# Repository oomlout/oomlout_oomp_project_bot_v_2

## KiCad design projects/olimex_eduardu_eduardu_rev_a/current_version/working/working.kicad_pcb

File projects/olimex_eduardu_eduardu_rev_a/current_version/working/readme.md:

# eduardu
 
## summary 
* id: olimex_eduardu_eduardu_rev_a
* user: olimex
* name: eduardu
* board: eduardu_rev_a
* repo: https://github.com/OLIMEX/eduArdu
* src_file_repo_kicad_pcb: HARDWARE/eduArdu_Rev_A/eduArdu_Rev_A.kicad_pcb
* src_file_repo_kicad_pcb_link: https://github.com/OLIMEX/eduArdu/tree/master/HARDWARE/eduArdu_Rev_A/eduArdu_Rev_A.kicad_pcb

* src_file_repo_sch: HARDWARE/eduArdu_Rev_A/eduArdu_Rev_A.sch
* src_file_repo_sch_link: https://github.com/OLIMEX/eduArdu/tree/master/HARDWARE/eduArdu_Rev_A/eduArdu_Rev_A.sch
* full details link: https://github.com/oomlout/oomlout_oomp_project_bot_v_2/tree/main/projects/olimex_eduardu_eduardu_rev_a/current_version/working

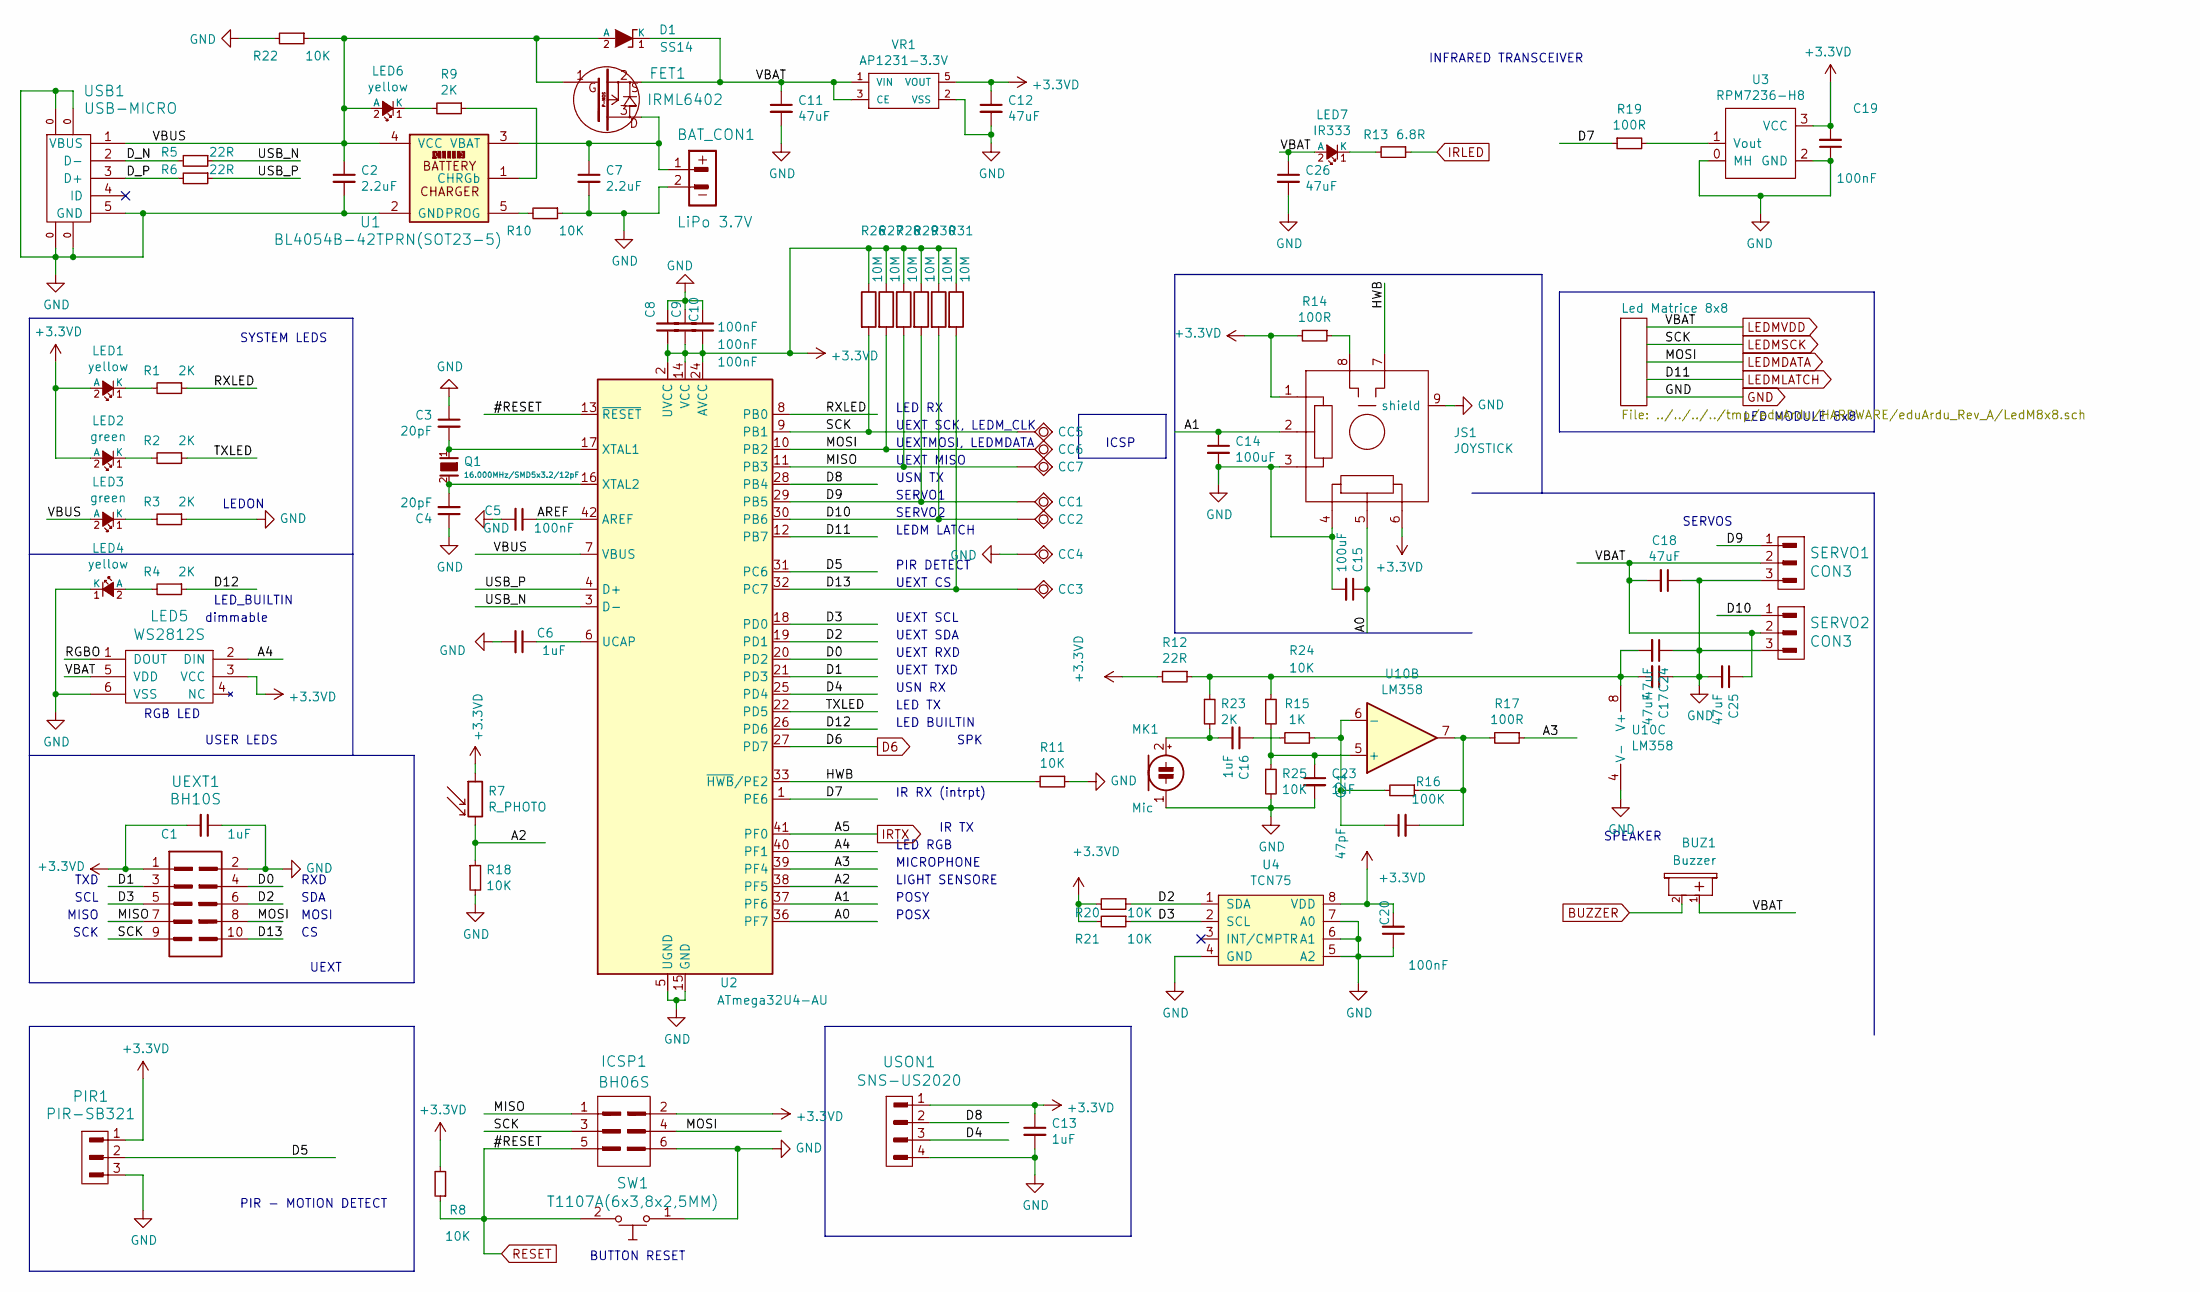
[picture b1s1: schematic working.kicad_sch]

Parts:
BAT_CON1: LiPo 3.7V; LIPO_BAT-CON2DW02R
BUZ1: Buzzer; BUZZER-PB1240
C1, C6, C13, C16, C23: 1uF; C_0603_5MIL_DWS
C2, C7: 2.2uF; C_0603_5MIL_DWS
C3, C4: 20pF; C_0402_5MIL_DWS
C5, C8, C9, C10, C19, C20: 100nF; C_0402_5MIL_DWS
C11, C12, C18, C26: 47uF; C_0805_5MIL_DWS
C14, C15: 100uF; C_0402_5MIL_DWS
C17, C24, C25: 47uF; C_0603_5MIL_DWS
C21: 47pF; C_0402_5MIL_DWS
CC1, CC2, CC3, CC4, CC5, CC6, CC7: TESTPAD; Mounting_hole_Shield_4.3mm
D1: SS14; SMA-KA
FET1: IRML6402; SOT23
ICSP1: BH06S; HN2x3
JS1: JOYSTICK
LED1, LED4, LED6: yellow; LED_0603_KA
LED2, LED3: green; LED_0603_KA
LED5: WS2812S; WS2812_NO_SILK
LED7: IR333; LED-5mm-PTH-AK
MK1: Mic; MIC
PIR1: PIR-SB321; HN1x3
Q1: 16.000MHz/SMD5x3.2/12pF; HCX-4S_2Pins_5.0x3.2mm
R1, R2, R3, R4, R9, R23: 2K; R_0402_5MIL_DWS
R5, R6, R12: 22R; R_0402_5MIL_DWS
R7: R_PHOTO
R8, R10, R11, R18, R20, R21, R22, R24, R25: 10K; R_0402_5MIL_DWS
R13: 6.8R; R_1206_5MIL_DWS
R14, R17, R19: 100R; R_0402_5MIL_DWS
R15: 1K; R_0402_5MIL_DWS
R16: 100K; R_0402_5MIL_DWS
R26, R27, R28, R29, R30, R31: 10M; R_0402_5MIL_DWS
SERVO1, SERVO2: CON3; HN1x3
SW1: T1107A(6x3,8x2,5MM)
U1: BL4054B-42TPRN(SOT23-5); SOT-23-5
U2: ATmega32U4-AU; TQFP44
U3: RPM7236-H8; RPM7236-H8-V
U4: TCN75; SO-8
U10: LM358; SO-8
UEXT1: BH10S; UEXTM-SMD
USB1: USB-MICRO; MICRO_USB_5P-F_TYPE_DIP
USON1: SNS-US2020; USONIC-PING
VR1: AP1231-3.3V; SOT-23-5

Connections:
+3.3VD: C1.2, C8.1, C9.1, C10.1, C12.1, C13.1, C19.2, C20.2, ICSP1.2, JS1.1, JS1.6, LED1.2 (A), LED2.2 (A), LED5.3 (VCC), PIR1.1, R7.1, R8.2, R12.2, R14.2, R20.2, R21.2, R26.1, R27.1, R28.1, R29.1, R30.1, R31.1, U2.2 (UVCC), U2.14 (VCC), U2.24 (AVCC), U2.34 (VCC), U2.44 (AVCC), U3.3 (VCC), U4.8 (VDD), UEXT1.1, USON1.1, VR1.5 (VOUT)
/A0: C15.1, JS1.5, U2.36 (PF7)
/A1: C14.1, JS1.2, U2.37 (PF6)
/A2: R7.2, R18.1, U2.38 (PF5)
/A3: R17.1, U2.39 (PF4)
/A4: LED5.2 (DIN), U2.40 (PF1)
/AREF: C5.1, U2.42 (AREF)
/D0: U2.20 (PD2), UEXT1.4
/D1: U2.21 (PD3), UEXT1.3
/D2: R20.1, U2.19 (PD1), U4.1 (SDA), UEXT1.6
/D3: R21.1, U2.18 (PD0), U4.2 (SCL), UEXT1.5
/D4: U2.25 (PD4), USON1.3
/D5: PIR1.2, U2.31 (PC6)
/D7: R19.1, U2.1 (PE6)
/D8: U2.28 (PB4), USON1.2
/D9: CC1.1, R29.2, SERVO1.1, U2.29 (PB5)
/D10: CC2.1, R30.2, SERVO2.1, U2.30 (PB6)
/D12: R4.1, U2.26 (PD6)
/D13: CC3.1, R31.2, U2.32 (PC7), UEXT1.10
/D_N: R5.2, USB1.2 (D-)
/D_P: R6.2, USB1.3 (D+)
/HWB: JS1.7, R11.2, U2.33 (~HWB/PE2)
/MISO: CC7.1, ICSP1.1, R28.2, U2.11 (PB3), UEXT1.7
/RGBO: LED5.1 (DOUT)
/RXLED: R1.1, U2.8 (PB0)
/TXLED: R2.1, U2.22 (PD5)
/USB_N: R5.1, U2.3 (D-)
/USB_P: R6.1, U2.4 (D+)
/VBUS: C2.1, D1.2 (A), FET1.1, LED3.2 (A), LED6.2 (A), R22.1, U1.4 (VCC), U2.7 (VBUS), USB1.1 (VBUS)
BUZZER: BUZ1.2 (MINUS); also elsewhere on the board
D6: U2.27 (PD7); also elsewhere on the board
GND: BAT_CON1.2, C1.1, C2.2, C3.1, C4.1, C5.2, C6.2, C7.2, C8.2, C9.2, C10.2, C11.2, C12.2, C13.2, C14.2, C15.2, C17.1, C18.1, C19.1, C20.1, C23.2, C24.1, C25.2, C26.2, CC4.1, ICSP1.6, JS1.3, JS1.4, JS1.9 (shield), LED4.1 (K), LED5.6 (VSS), MK1.1 (-), PIR1.3, R3.1, R10.1, R11.1, R18.2, R22.2, R25.2, SERVO1.3, SERVO2.3, SW1.1, U1.2 (GND), U2.5 (UGND), U2.15 (GND), U2.23 (GND), U2.35 (GND), U2.43 (GND), U3.0 (MH), U3.2 (GND), U4.4 (GND), U4.5 (A2), U4.6 (A1), U4.7 (A0), U10.4 (V-), UEXT1.2, USB1.0, USB1.5 (GND), USON1.4, VR1.2 (VSS); also elsewhere on the board
IRLED: R13.1; also elsewhere on the board
IRTX: U2.41 (PF0); also elsewhere on the board
LEDMDATA: CC6.1, ICSP1.4, R27.2, U2.10 (PB2), UEXT1.8; also elsewhere on the board
LEDMLATCH: U2.12 (PB7); also elsewhere on the board
LEDMSCK: CC5.1, ICSP1.3, R26.2, U2.9 (PB1), UEXT1.9; also elsewhere on the board
LEDMVDD: BUZ1.1 (PLUS), C11.1, C18.2, C25.1, C26.1, D1.1 (K), FET1.2, LED5.5 (VDD), LED7.2 (A), SERVO1.2, SERVO2.2, VR1.1 (VIN), VR1.3 (CE); also elsewhere on the board
unnamed: BAT_CON1.1, C7.1, FET1.3, U1.3 (VBAT)
unnamed: C3.2, Q1.1, U2.17 (XTAL1)
unnamed: C4.2, Q1.2, U2.16 (XTAL2)
unnamed: C6.1, U2.6 (UCAP)
unnamed: C16.1, R15.2
unnamed: C16.2, MK1.2 (+), R23.2
unnamed: C17.2, C24.2, R12.1, R23.1, R24.1, U10.8 (V+)
unnamed: C21.1, R15.1, R16.2, U10.6 (-)
unnamed: C21.2, R16.1, R17.2, U10.7
unnamed: C23.1, R24.2, R25.1, U10.5 (+)
unnamed: JS1.8, R14.1
unnamed: LED1.1 (K), R1.2
unnamed: LED2.1 (K), R2.2
unnamed: LED3.1 (K), R3.2
unnamed: LED4.2 (A), R4.2
unnamed: LED6.1 (K), R9.2
unnamed: LED7.1 (K), R13.2
unnamed: R9.1, U1.1 (CHRGb)
unnamed: R10.2, U1.5 (PROG)
unnamed: R19.2, U3.1 (Vout)
RESET: ICSP1.5, R8.1, SW1.2, U2.13 (~RESET); also elsewhere on the board

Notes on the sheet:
PIR - MOTION DETECT
IR TX
SDA
UEXT TXD
UEXT CS
RGB LED
MICROPHONE
SERVO2
LED_BUILTIN
ICSP
UEXT MISO
UEXT SCL
SERVO1
POSX
PIR DETECT
INFRARED TRANSCEIVER
SERVOS
LED BUILTIN
LED TX
dimmable
UEXT SCK, LEDM_CLK
LED MODULE 8x8
UEXT SDA
LEDON
LED RGB
LED RX
TXD
POSY
UEXT
USN RX
MOSI
USER LEDS
LEDM LATCH
RXD
IR RX (intrpt)
LIGHT SENSORE
SPEAKER
SCK
BUTTON RESET
SPK

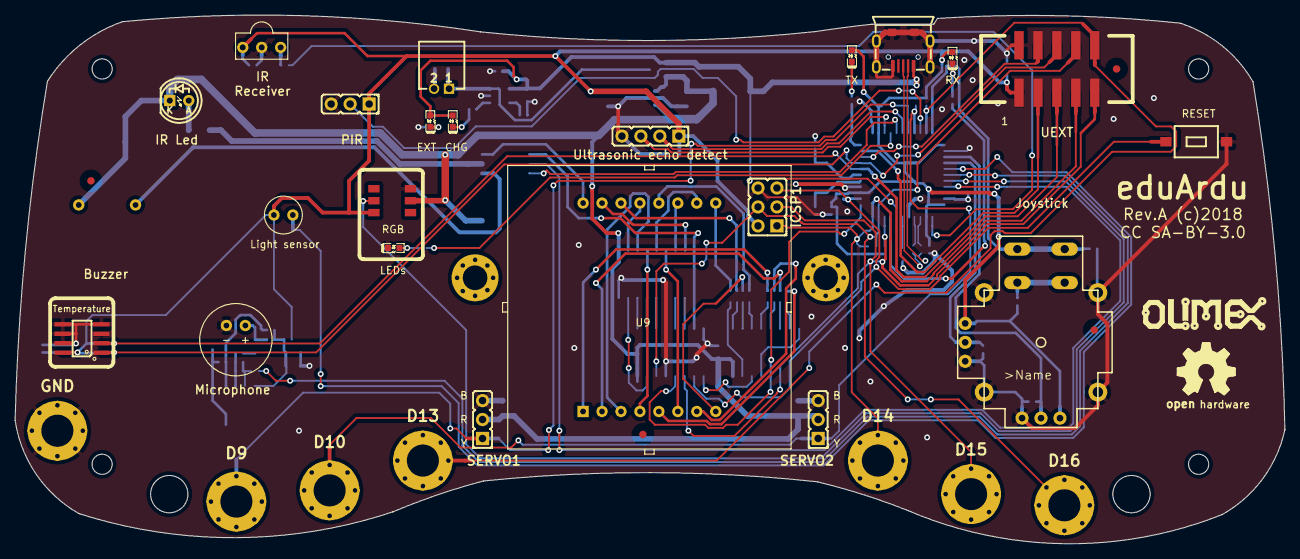
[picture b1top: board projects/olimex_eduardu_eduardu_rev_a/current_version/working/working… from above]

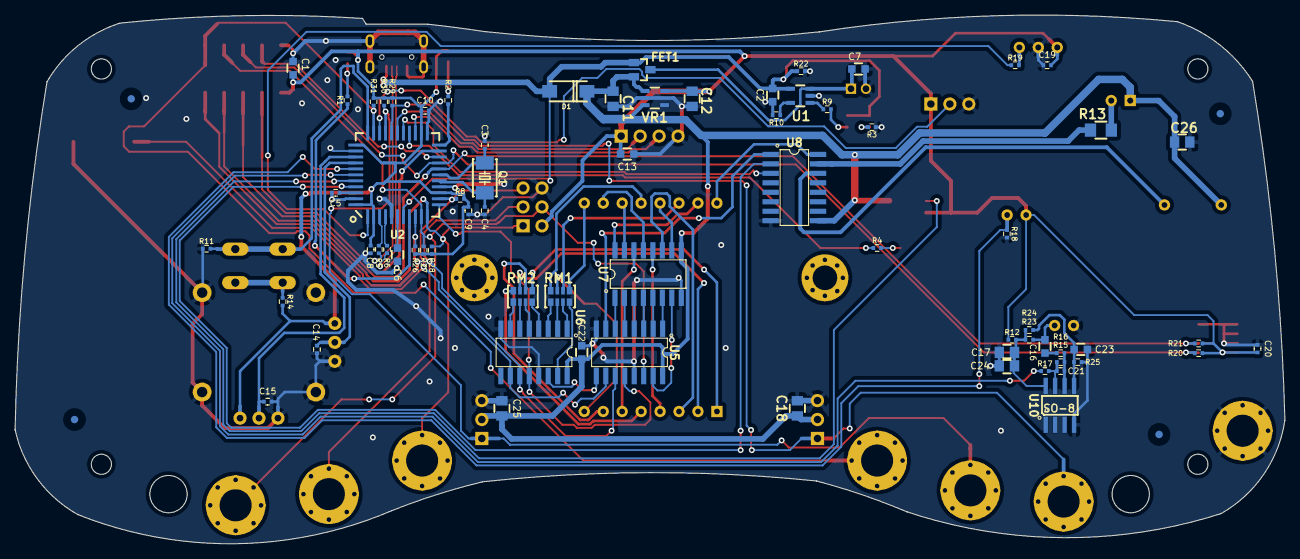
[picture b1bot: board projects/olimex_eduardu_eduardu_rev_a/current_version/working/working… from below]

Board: 2 copper layers, 170.2 x 70.9 mm, 115 parts (73 on the bottom side), 91 nets.

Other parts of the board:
C22: 1uF; C_0603_5MIL_DWS
MountingHole: NPTH_2.7mm
MountingHole#2, MountingHole#3, MountingHole#4, MountingHole#5, MountingHole#6: NPTH_2.7mm
MountingHoleShield**: Mounting_hole_Shield_3.3mm
MountingHoleShield**#2: Mounting_hole_Shield_3.3mm
RM1, RM2: RA1206_(4x0603)_4B8_22R; RA1206_(4X0603)_4B8_mine
Ref*: Val**; Fiducial1x3_transp
Ref*#2, Ref*#3, Ref*#4, Ref*#5, Ref*#6, Ref*#7, Ref*#8: Val**; Fiducial1x3_transp
U5, U6: 74HC595; SO-16
U7, U8: ULN2003AD; SO-16
U9: GYX1588AB-RESCUE-BADGE-LED8x8_Rev.A; GYX1588AB

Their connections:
/Led Matrice 8x8/C1: U7.10, U9.13
/Led Matrice 8x8/C2: U7.11, U9.3
/Led Matrice 8x8/C3: U7.12, U9.4
/Led Matrice 8x8/C4: U7.13, U9.10
/Led Matrice 8x8/C5: U7.14, U9.6
/Led Matrice 8x8/C6: U7.15, U9.11
/Led Matrice 8x8/C7: U7.16, U9.15
/Led Matrice 8x8/C8: U8.16, U9.16
/Led Matrice 8x8/R1: RM1.5, U9.9
/Led Matrice 8x8/R2: RM1.6, U9.14
/Led Matrice 8x8/R3: RM1.7, U9.8
/Led Matrice 8x8/R4: RM1.8, U9.12
/Led Matrice 8x8/R5: RM2.5, U9.1
/Led Matrice 8x8/R6: RM2.6, U9.7
/Led Matrice 8x8/R7: RM2.7, U9.2
/Led Matrice 8x8/R8: RM2.8, U9.5
BUZZER: U8.14; also elsewhere on the board
D6: U8.3; also elsewhere on the board
GND: C22.2, U5.8, U5.13, U6.8, U6.13, U7.8, U8.8; also elsewhere on the board
IRLED: U8.15; also elsewhere on the board
IRTX: U8.2; also elsewhere on the board
LEDMDATA: U5.14; also elsewhere on the board
LEDMLATCH: U5.12, U6.12; also elsewhere on the board
LEDMSCK: U5.11, U6.11; also elsewhere on the board
LEDMVDD: C22.1, U5.16, U6.16, U7.9, U8.9; also elsewhere on the board
unnamed: RM1.1, U6.3
unnamed: RM1.2, U6.2
unnamed: RM1.3, U6.1
unnamed: RM1.4, U6.15
unnamed: RM2.1, U6.7
unnamed: RM2.2, U6.6
unnamed: RM2.3, U6.5
unnamed: RM2.4, U6.4
unnamed: U5.1, U7.6
unnamed: U5.2, U7.5
unnamed: U5.3, U7.4
unnamed: U5.4, U7.3
unnamed: U5.5, U7.2
unnamed: U5.6, U7.1
unnamed: U5.7, U8.1
unnamed: U5.9, U6.14
unnamed: U5.15, U7.7
RESET: U5.10, U6.10; also elsewhere on the board

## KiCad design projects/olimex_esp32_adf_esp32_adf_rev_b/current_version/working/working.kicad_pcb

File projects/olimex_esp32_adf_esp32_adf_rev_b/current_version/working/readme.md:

# esp32_adf
 
## summary 
* id: olimex_esp32_adf_esp32_adf_rev_b
* user: olimex
* name: esp32_adf
* board: esp32_adf_rev_b
* repo: https://github.com/OLIMEX/ESP32-ADF
* src_file_repo_kicad_pcb: HARDWARE/ESP32-ADF Rev.B/ESP32-ADF_Rev_B.kicad_pcb
* src_file_repo_kicad_pcb_link: https://github.com/OLIMEX/ESP32-ADF/tree/master/HARDWARE/ESP32-ADF Rev.B/ESP32-ADF_Rev_B.kicad_pcb

* src_file_repo_sch: HARDWARE/ESP32-ADF Rev.B/ESP32-ADF_Rev_B.sch
* src_file_repo_sch_link: https://github.com/OLIMEX/ESP32-ADF/tree/master/HARDWARE/ESP32-ADF Rev.B/ESP32-ADF_Rev_B.sch
* full details link: https://github.com/oomlout/oomlout_oomp_project_bot_v_2/tree/main/projects/olimex_esp32_adf_esp32_adf_rev_b/current_version/working

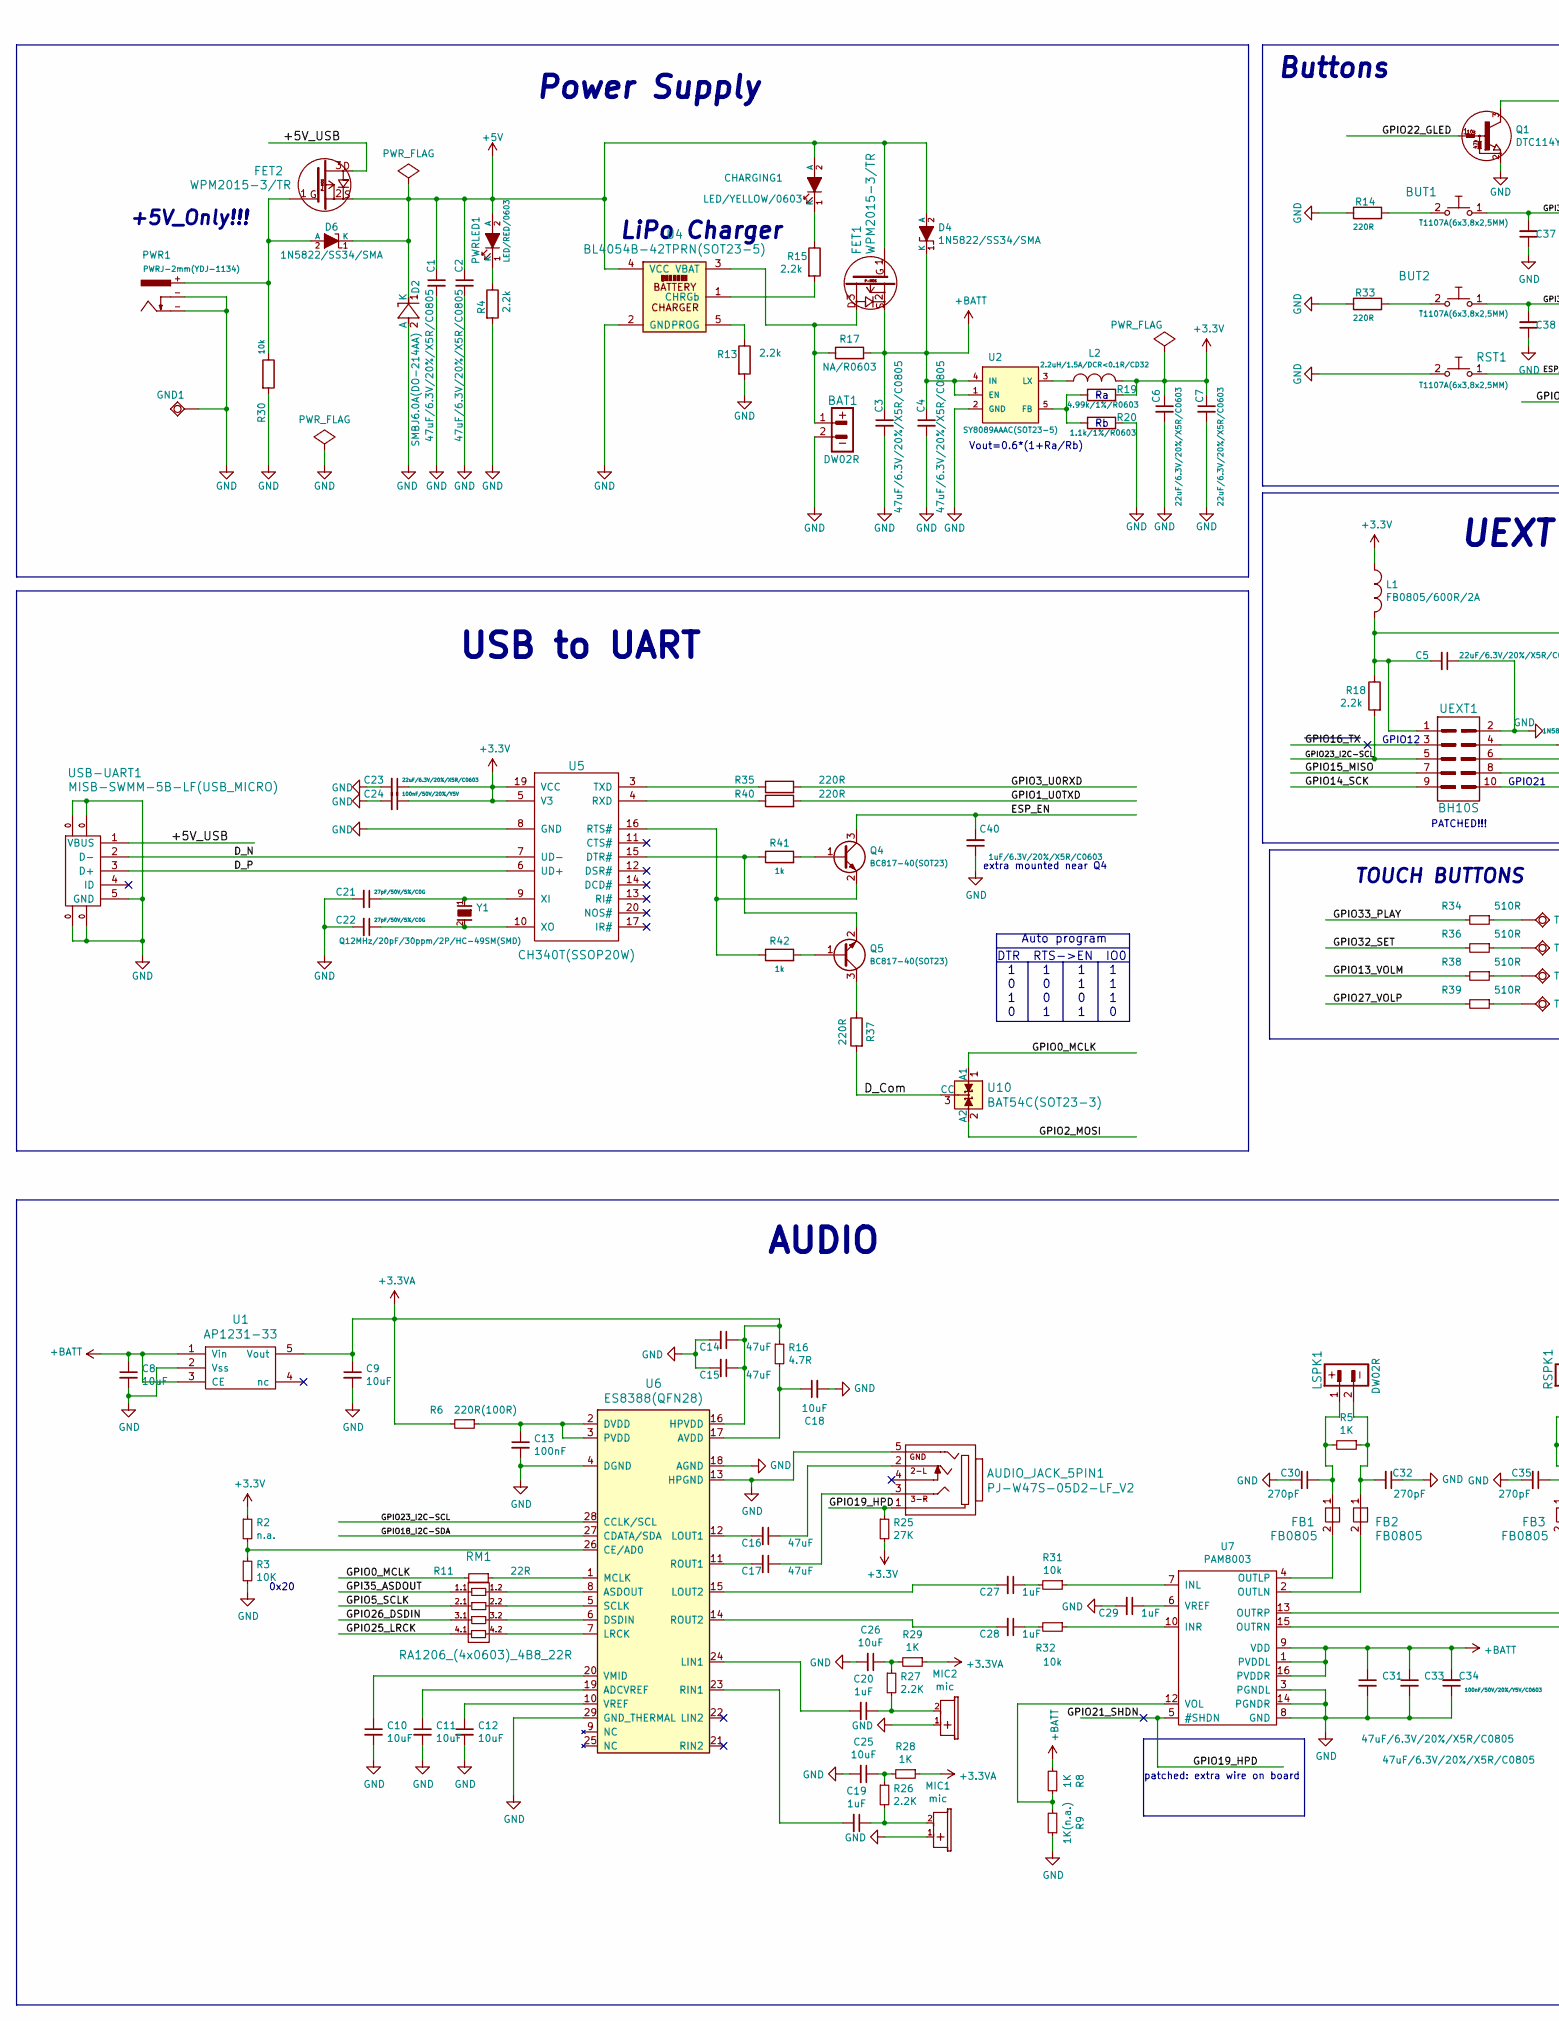
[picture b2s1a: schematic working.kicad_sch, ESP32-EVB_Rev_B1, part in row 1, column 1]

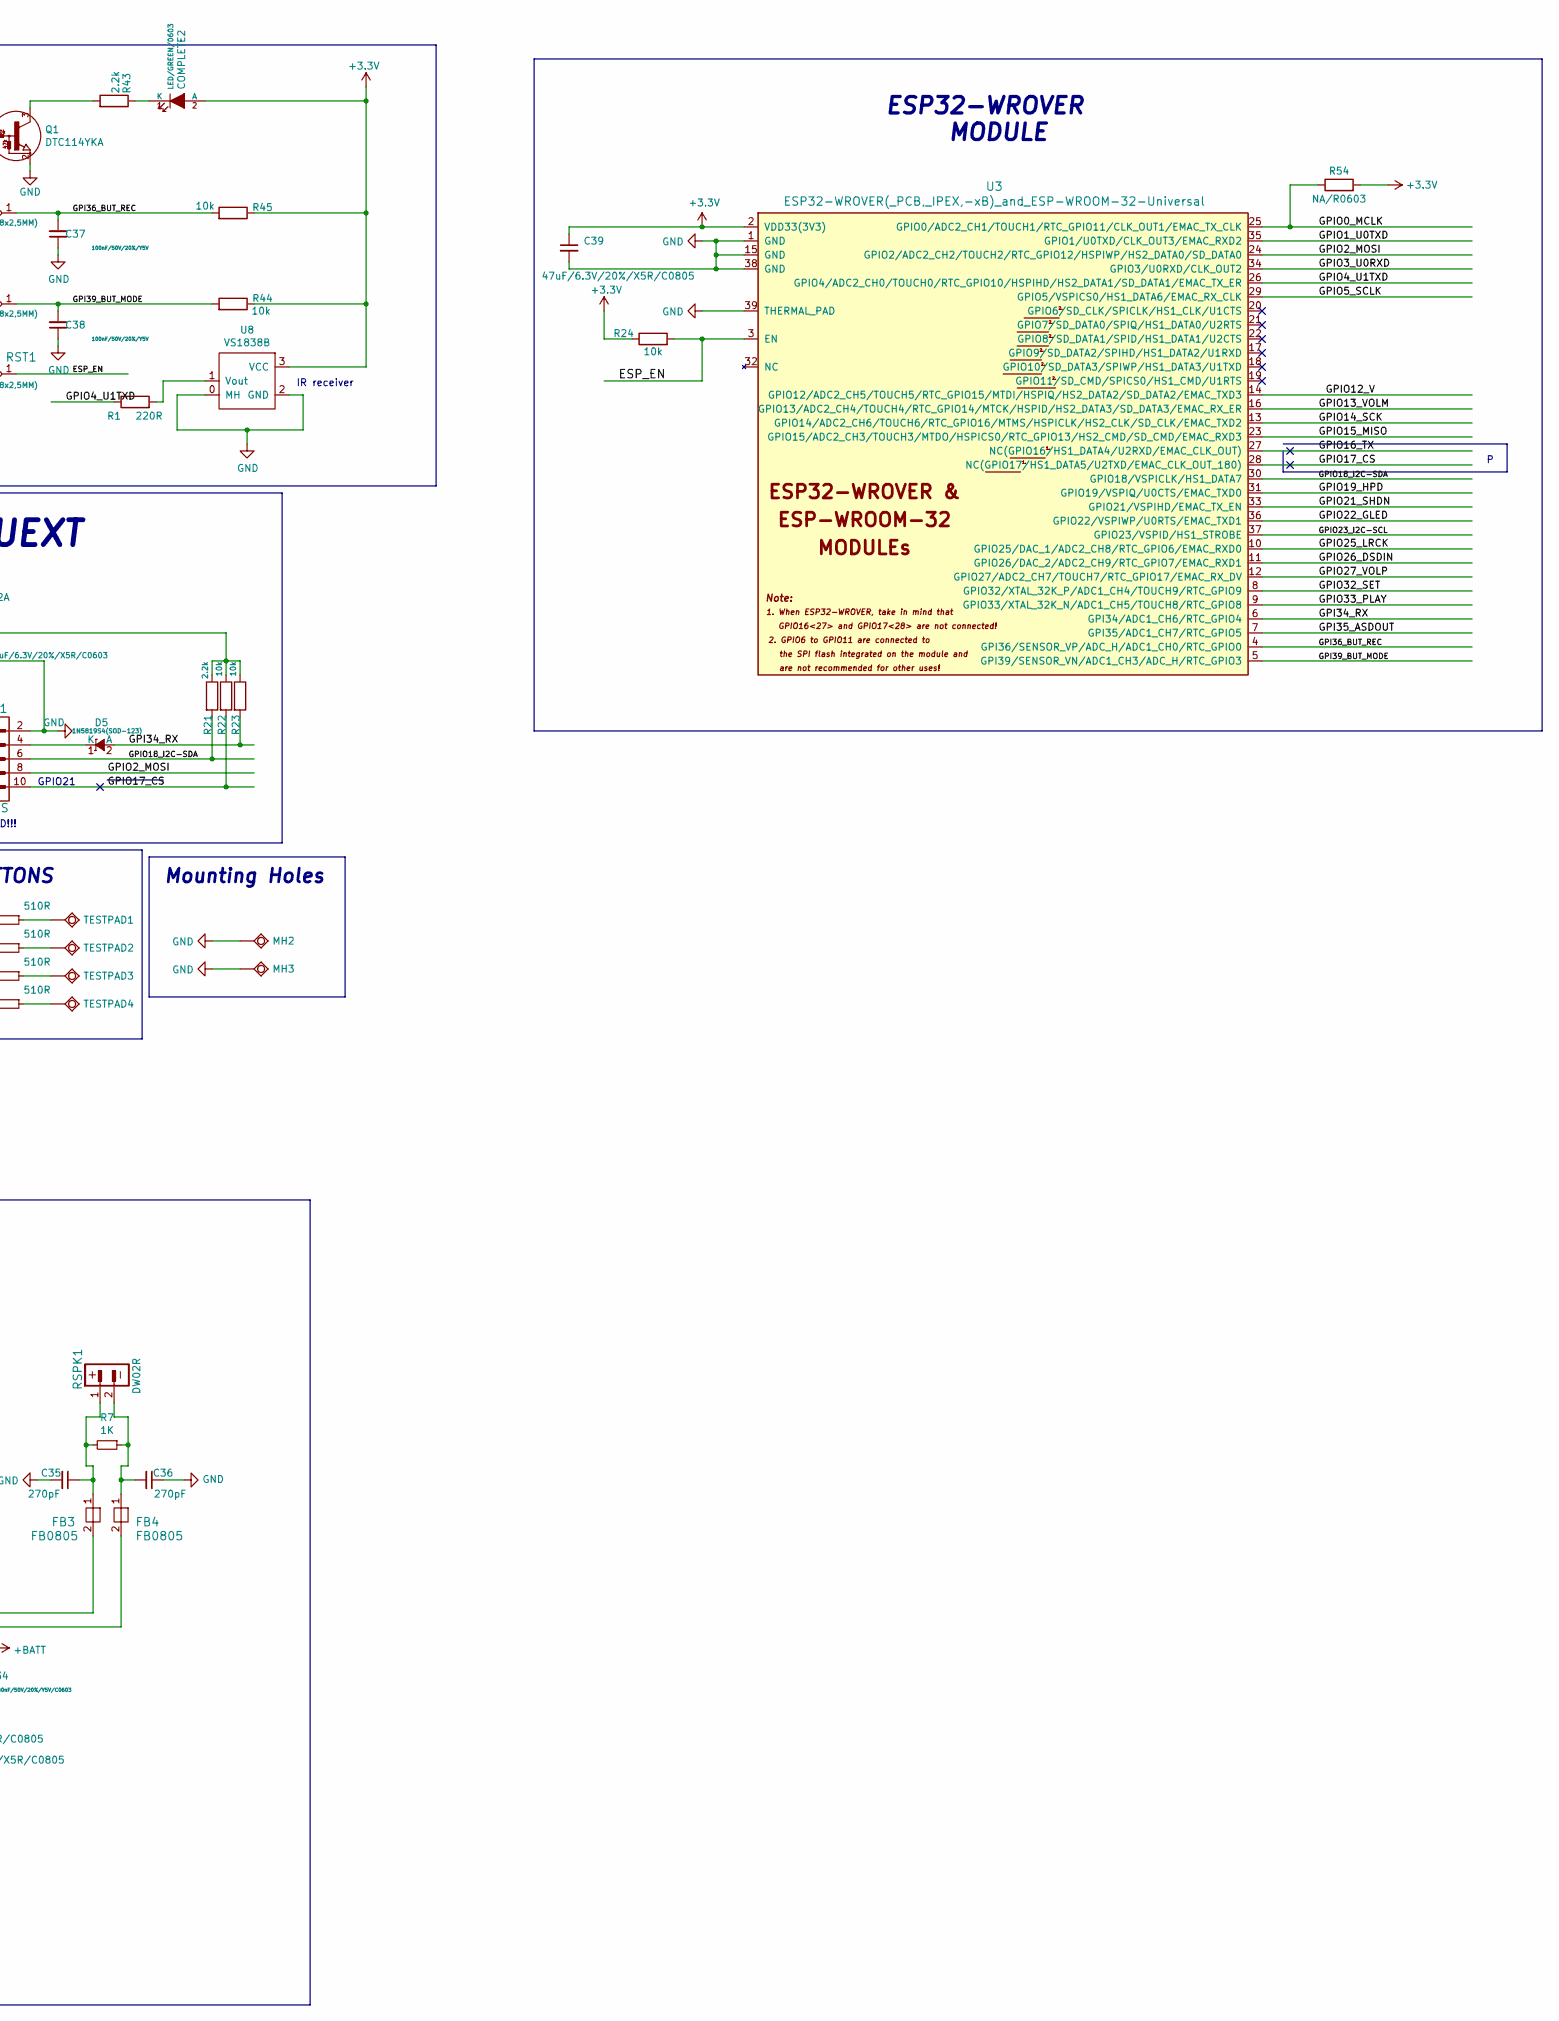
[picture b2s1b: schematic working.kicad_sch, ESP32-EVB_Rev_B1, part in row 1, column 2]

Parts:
AUDIO_JACK_5PIN1: PJ-W47S-05D2-LF_V2; PJ-W47S-05D2-LF_5PIN_V2
BAT1: DW02R; LIPO_BAT-CON2DW02R
BUT1, BUT2: T1107A(6x3,8x2,5MM)
C1, C2, C3, C4, C31, C33, C39: 47uF/6.3V/20%/X5R/C0805; C_0805_5MIL_DWS
C5, C6, C7, C23: 22uF/6.3V/20%/X5R/C0603; C_0603_5MIL_DWS
C8, C9, C10, C11, C12, C18, C25, C26: 10uF; C_0603_5MIL_DWS
C13: 100nF; C_0603_5MIL_DWS
C14, C15, C16, C17: 47uF; C_0805_5MIL_DWS
C19, C20, C27, C28, C29: 1uF; C_0603_5MIL_DWS
C21, C22: 27pF/50V/5%/C0G; C_0603_5MIL_DWS
C24: 100nF/50V/20%/Y5V; C_0603_5MIL_DWS
C30, C32, C35, C36: 270pF; C_0402_5MIL_DWS
C34: 100nF/50V/20%/Y5V/C0603; C_0402_5MIL_DWS
C37, C38: 100nF/50V/20%/Y5V; C_0402_5MIL_DWS
C40: 1uF/6.3V/20%/X5R/C0603; C_0603_5MIL_DWS
CHARGING1: LED/YELLOW/0603; LED_0603_KA
COMPLETE2: LED/GREEN/0603; LED_0603_KA
D2: SMBJ6.0A(DO-214AA); DO214AA_1(K)-2(A)
D4, D6: 1N5822/SS34/SMA; SMA-KA
D5: 1N5819S4(SOD-123); SOD-123_1C-2A_KA
FB1, FB2, FB3, FB4: FB0805; L_0805_5MIL_DWS
FET1, FET2: WPM2015-3/TR; SOT23
GND1: TESTPAD; TESTPAD_40-ROUND
L1: FB0805/600R/2A; L_0805_5MIL_DWS
L2: 2.2uH/1.5A/DCR<0.1R/CD32; CD32
LSPK1: DW02R; LIPO_BAT-CON2DW02R
MH2, MH3: Mounting_hole_Shield_3.3mm
MIC1, MIC2: mic; MIC
PWR1: PWRJ-2mm(YDJ-1134); PWRJ-2mm(YDJ-1136)
PWRLED1: LED/RED/0603; LED_0603_KA
Q1: DTC114YKA; SOT23
Q4, Q5: BC817-40(SOT23); SOT23
R1, R14, R33, R35, R37, R40: 220R; R_0402_5MIL_DWS
R2: n.a.; R_0402_5MIL_DWS
R3: 10K; R_0402_5MIL_DWS
R4, R13, R15, R18, R21, R43: 2.2k; R_0402_5MIL_DWS
R5, R7, R8, R28, R29: 1K; R_0402_5MIL_DWS
R6: 220R(100R); R_0402_5MIL_DWS
R9: 1K(n.a.); R_0402_5MIL_DWS
R11: 22R; R_0402_5MIL_DWS
R16: 4.7R; R_0402_5MIL_DWS
R17, R54: NA/R0603; R_0402_5MIL_DWS
R19: 4.99k/1%/R0603; R_0603_5MIL_DWS
R20: 1.1k/1%/R0603; R_0603_5MIL_DWS
R22, R23, R24, R30, R31, R32, R44, R45: 10k; R_0402_5MIL_DWS
R25: 27K; R_0402_5MIL_DWS
R26, R27: 2.2K; R_0402_5MIL_DWS
R34, R36, R38, R39: 510R; R_0402_5MIL_DWS
R41, R42: 1k; R_0402_5MIL_DWS
RM1: RA1206_(4x0603)_4B8_22R; RA1206_(4X0603)_4B8_mine_1.1
RSPK1: DW02R; LIPO_BAT-CON2DW02R
RST1: T1107A(6x3,8x2,5MM)
TESTPAD1, TESTPAD2, TESTPAD3, TESTPAD4: TESTPAD; TP_SMD_10.00x5.00mm
U1: AP1231-33; SOT-23-5
U2: SY8089AAAC(SOT23-5); SOT-23-5
U3: ESP32-WROVER(_PCB,_IPEX,-xB)_and_ESP-WROOM-32-Uni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; ESP32-WROVER_MODULE_
U4: BL4054B-42TPRN(SOT23-5); SOT-23-5
U5: CH340T(SSOP20W); SSOP-20W
U6: ES8388(QFN28); QFN28_EP(29)_4.076x4.076x0.9mm_Pitch_0.45mm
U7: PAM8003; SO-16
U8: VS1838B; RPM7236-H8
U10: BAT54C(SOT23-3); SOT23
UEXT1: BH10S; GBH-254-SMT-10_Smaller
USB-UART1: MISB-SWMM-5B-LF(USB_MICRO); USB-MICRO_MISB-SWMM-5B_LF
Y1: Q12MHz/20pF/30ppm/2P/HC-49SM(SMD); TSX-3.2x2.5mm_GND(3)

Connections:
+3.3VA: C9.1, C14.1, C15.1, R6.2, R16.1, R28.1, R29.1, U1.5 (Vout), U6.16 (HPVDD)
+3V3: C6.1, C7.1, C23.1, C24.1, C39.1, COMPLETE2.2 (A), L1.1, L2.2, R2.1, R19.2, R24.1, R25.2, R44.1, R45.1, R54.2, U3.2 (VDD33(3V3)), U5.5 (V3), U5.19 (VCC), U8.3 (VCC)
+5V: C1.1, C2.1, CHARGING1.2 (A), D2.1 (K), D4.2 (A), D6.1 (K), FET1.1, FET2.2, PWRLED1.2 (A), U4.4 (VCC)
+BATT: C3.1, C4.1, C8.1, C31.1, C33.1, C34.2, D4.1 (K), FET1.2, R8.2, R17.2, U1.1 (Vin), U1.3 (CE), U2.1 (EN), U2.4 (IN), U7.1 (PVDDL), U7.9 (VDD), U7.16 (PVDDR)
/+5V_USB: FET2.3, USB-UART1.1 (VBUS)
/D_Com: R37.2, U10.3 (CC)
/D_N: U5.7 (UD-), USB-UART1.2 (D-)
/D_P: U5.6 (UD+), USB-UART1.3 (D+)
/ESP_EN: C40.2, Q4.3 (C), R24.2, RST1.1, U3.3 (EN)
/GPI34_RX: D5.2 (A), R23.2, U3.6 (GPI34/ADC1_CH6/RTC_GPIO4)
/GPI35_ASDOUT: RM1.1.1, U3.7 (GPI35/ADC1_CH7/RTC_GPIO5)
/GPI36_BUT_REC: BUT1.1, C37.2, R45.2, U3.4 (GPI36/SENSOR_VP/ADC_H/ADC1_CH0/RTC_GPIO0)
/GPI39_BUT_MODE: BUT2.1, C38.2, R44.2, U3.5 (GPI39/SENSOR_VN/ADC1_CH3/ADC_H/RTC_GPIO3)
/GPIO0_MCLK: R11.2, R54.1, U3.25 (GPIO0/ADC2_CH1/TOUCH1/RTC_GPIO11/CLK_OU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), U10.1 (A1)
/GPIO1_U0TXD: R40.2, U3.35 (GPIO1/U0TXD/CLK_OUT3/EMAC_RXD2)
/GPIO2_MOSI: U3.24 (GPIO2/ADC2_CH2/TOUCH2/RTC_GPIO12/HSPIWP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), U10.2 (A2), UEXT1.8
/GPIO3_U0RXD: R35.2, U3.34 (GPIO3/U0RXD/CLK_OUT2)
/GPIO4_U1TXD: R1.1, U3.26 (GPIO4/ADC2_CH0/TOUCH0/RTC_GPIO10/HSPIHD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)
/GPIO5_SCLK: RM1.2.1, U3.29 (GPIO5/VSPICS0/HS1_DATA6/EMAC_RX_CLK)
/GPIO12_V: U3.14 (GPIO12/ADC2_CH5/TOUCH5/RTC_GPIO15/MTDI/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)
/GPIO13_VOLM: R38.2, U3.16 (GPIO13/ADC2_CH4/TOUCH4/RTC_GPIO14/MTCK/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)
/GPIO14_SCK: U3.13 (GPIO14/ADC2_CH6/TOUCH6/RTC_GPIO16/MTMS/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), UEXT1.9
/GPIO15_MISO: U3.23 (GPIO15/ADC2_CH3/TOUCH3/MTDO/HSPICS0/RTC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), UEXT1.7
/GPIO16_TX: U3.27 (NC(GPIO16/HS1_DATA4/U2RXD/EMAC_CLK_OUT)), UEXT1.3
/GPIO17_CS: R22.2, U3.28 (NC(GPIO17/HS1_DATA5/U2TXD/EMAC_CLK_OUT_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), UEXT1.10
/GPIO18_I2C-SDA: R21.2, U3.30 (GPIO18/VSPICLK/HS1_DATA7), U6.27 (CDATA/SDA), UEXT1.6
/GPIO22_GLED: Q1.1 (B), U3.36 (GPIO22/VSPIWP/U0RTS/EMAC_TXD1)
/GPIO23_I2C-SCL: R18.2, U3.37 (GPIO23/VSPID/HS1_STROBE), U6.28 (CCLK/SCL), UEXT1.5
/GPIO25_LRCK: RM1.4.1, U3.10 (GPIO25/DAC_1/ADC2_CH8/RTC_GPIO6/EMAC_RX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)
/GPIO26_DSDIN: RM1.3.1, U3.11 (GPIO26/DAC_2/ADC2_CH9/RTC_GPIO7/EMAC_RX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)
/GPIO27_VOLP: R39.2, U3.12 (GPIO27/ADC2_CH7/TOUCH7/RTC_GPIO17/EMAC_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)
/GPIO32_SET: R36.2, U3.8 (GPIO32/XTAL_32K_P/ADC1_CH4/TOUCH9/RTC_G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)
/GPIO33_PLAY: R34.2, U3.9 (GPIO33/XTAL_32K_N/ADC1_CH5/TOUCH8/RTC_G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)
GND: AUDIO_JACK_5PIN1.5, BAT1.2, C1.2, C2.2, C3.2, C4.2, C5.1, C6.2, C7.2, C8.2, C9.2, C10.2, C11.2, C12.2, C13.2, C14.2, C15.2, C18.2, C21.2, C22.2, C23.2, C24.2, C25.2, C26.2, C29.2, C30.2, C31.2, C32.1, C33.2, C34.1, C35.2, C36.1, C37.1, C38.1, C39.2, C40.1, D2.2 (A), GND1.1, MH2.GND1, MH3.GND1, MIC1.1 (PLUS), MIC2.1 (PLUS), PWR1.-, Q1.2 (E), R3.2, R4.2, R9.1, R13.2, R14.2, R20.2, R30.2, R33.2, RST1.2, U1.2 (Vss), U2.2 (GND), U3.1 (GND), U3.15 (GND), U3.38 (GND), U3.39 (THERMAL_PAD), U4.2 (GND), U5.8 (GND), U6.4 (DGND), U6.13 (HPGND), U6.18 (AGND), U6.29 (GND_THERMAL), U7.3 (PGNDL), U7.8 (GND), U7.14 (PGNDR), U8.0 (MH), U8.2 (GND), UEXT1.2, USB-UART1.0, USB-UART1.5 (GND); also elsewhere on the board
unnamed: AUDIO_JACK_5PIN1.2, C16.1
unnamed: AUDIO_JACK_5PIN1.3, C17.1
unnamed: BAT1.1, FET1.3, R17.1, U4.3 (VBAT)
unnamed: BUT1.2, R14.1
unnamed: BUT2.2, R33.1
unnamed: C5.2, L1.2, R18.1, R21.1, R22.1, R23.1, UEXT1.1
unnamed: C10.1, U6.20 (VMID)
unnamed: C11.1, U6.19 (ADCVREF)
unnamed: C12.1, U6.10 (VREF)
unnamed: C13.1, R6.1, U6.2 (DVDD), U6.3 (PVDD)
unnamed: C16.2, U6.12 (LOUT1)
unnamed: C17.2, U6.11 (ROUT1)
unnamed: C18.1, R16.2, U6.17 (AVDD)
unnamed: C19.1, MIC1.2 (MINUS), R26.2
unnamed: C19.2, U6.23 (RIN1)
unnamed: C20.1, MIC2.2 (MINUS), R27.2
unnamed: C20.2, U6.24 (LIN1)
unnamed: C21.1, U5.9 (XI), Y1.1
unnamed: C22.1, U5.10 (XO), Y1.2
unnamed: C25.1, R26.1, R28.2
unnamed: C26.1, R27.1, R29.2
unnamed: C27.1, R31.2
unnamed: C27.2, U6.15 (LOUT2)
unnamed: C28.1, R32.2
unnamed: C28.2, U6.14 (ROUT2)
unnamed: C29.1, U7.6 (VREF)
unnamed: C30.1, FB1.1, LSPK1.1, R5.2
unnamed: C32.2, FB2.1, LSPK1.2, R5.1
unnamed: C35.1, FB3.1, R7.2, RSPK1.1
unnamed: C36.2, FB4.1, R7.1, RSPK1.2
unnamed: CHARGING1.1 (K), R15.1
unnamed: COMPLETE2.1 (K), R43.1
unnamed: D5.1 (K), UEXT1.4
unnamed: D6.2 (A), FET2.1, PWR1.+, R30.1
unnamed: FB1.2, U7.4 (OUTLP)
unnamed: FB2.2, U7.2 (OUTLN)
unnamed: FB3.2, U7.13 (OUTRP)
unnamed: FB4.2, U7.15 (OUTRN)
unnamed: L2.1, U2.3 (LX)
unnamed: PWRLED1.1 (K), R4.1
unnamed: Q1.3 (C), R43.2
unnamed: Q4.1 (B), R41.2
unnamed: Q4.2 (E), R42.1, U5.16 (RTS#)
unnamed: Q5.1 (B), R42.2
unnamed: Q5.2 (E), R41.1, U5.15 (DTR#)
unnamed: Q5.3 (C), R37.1
unnamed: R1.2, U8.1 (Vout)
unnamed: R2.2, R3.1, U6.26 (CE/AD0)
unnamed: R8.1, R9.2, U7.12 (VOL)
unnamed: R11.1, U6.1 (MCLK)
unnamed: R13.1, U4.5 (PROG)
unnamed: R15.2, U4.1 (CHRGb)
unnamed: R19.1, R20.1, U2.5 (FB)
unnamed: R31.1, U7.7 (INL)
unnamed: R32.1, U7.10 (INR)
unnamed: R34.1, TESTPAD1.1
unnamed: R35.1, U5.3 (TXD)
unnamed: R36.1, TESTPAD2.1
unnamed: R38.1, TESTPAD3.1
unnamed: R39.1, TESTPAD4.1
unnamed: R40.1, U5.4 (RXD)
unnamed: RM1.1.2, U6.8 (ASDOUT)
unnamed: RM1.2.2, U6.5 (SCLK)
unnamed: RM1.3.2, U6.6 (DSDIN)
unnamed: RM1.4.2, U6.7 (LRCK)

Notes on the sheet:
Buttons
DTR RTS->EN IO0
ESP32-WROVER MODULE
PATCHED!!!
Auto program
0x20
extra mounted near Q4
USB to UART
IR receiver
GPIO12
TOUCH BUTTONS
AUDIO
+5V_Only!!!
LiPo Charger
Vout=0.6*(1+Ra/Rb)
UEXT
patched: extra wire on board
Power Supply
GPIO21
Mounting Holes

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
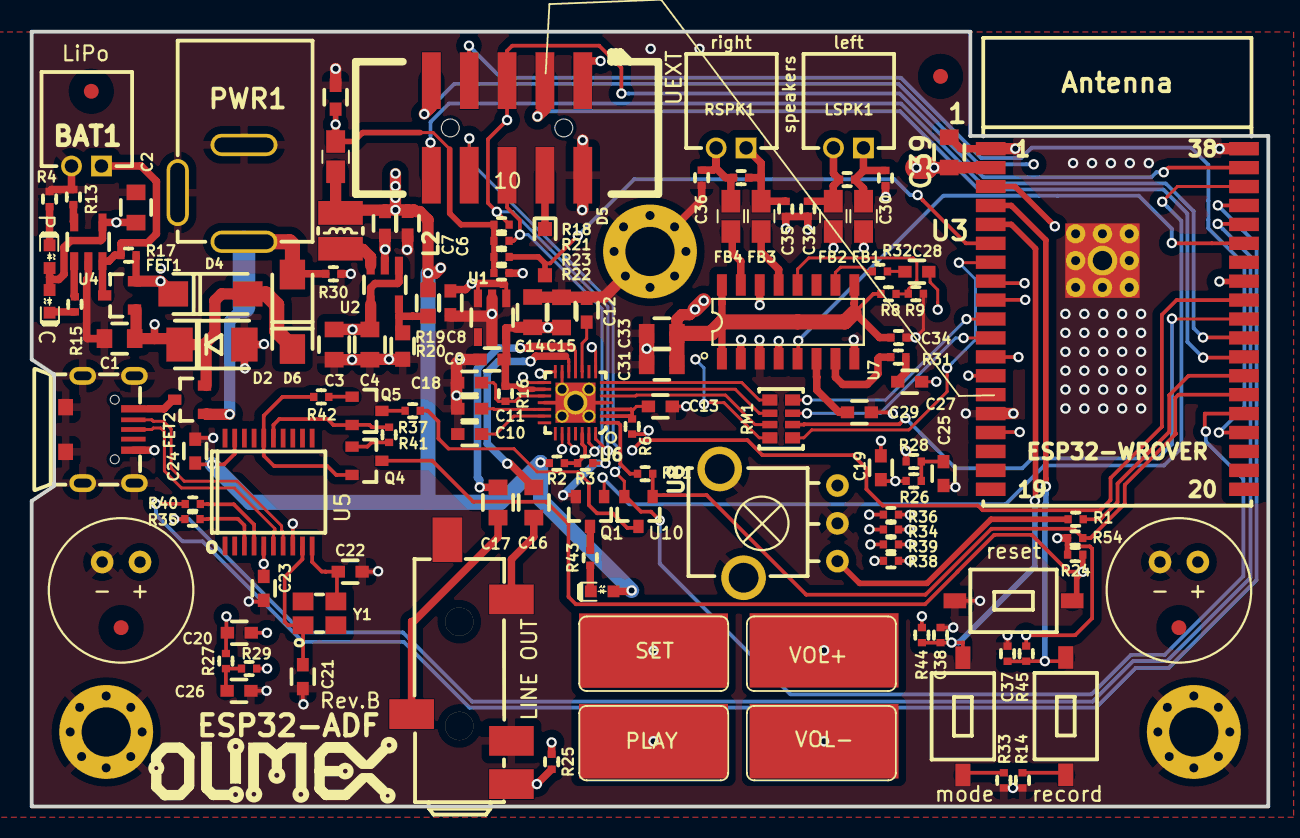
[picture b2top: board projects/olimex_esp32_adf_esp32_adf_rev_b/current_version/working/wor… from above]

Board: 4 copper layers, 83.0 x 52.0 mm, 136 parts (1 on the bottom side), 100 nets.

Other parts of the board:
MH3#2: Mounting_hole_Shield_3.3mm
Ref*: Val**; Fiducial1x3_transp
Ref*#2, Ref*#3, Ref*#4: Val**; Fiducial1x3_transp
Ref**: Val**; LOGO_ANTISTATIC_SMALL_4.5mmX2.8mm

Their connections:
GND: MH3#2.GND1; also elsewhere on the board

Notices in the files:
projects/olimex_eduardu_eduardu_rev_a/current_version/working/working.kicad_pcb:
Rev.A (c)2018
projects/olimex_esp32_c3_devkit_lipo_esp32_c3_devkit_lipo_rev_a/current_version/working/working.kicad_pcb:
(C) 2022
projects/olimex_esp32_c6_evb_esp32_c6_evb_rev_a/current_version/working/working.kicad_pcb:
(C) 2023
